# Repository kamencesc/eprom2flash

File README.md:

# untested

# eprom2flash
Use 29F800 flash memory on a 27C800 and 27C160 socket.

**Only works on 16 bit mode!**

# Configure
To use 1 Bank (as a 27C800), use Bank 1 and close jumpers "B1 only".

To use 2 Bank (as a 27c160), use a 74x139 tsop16.

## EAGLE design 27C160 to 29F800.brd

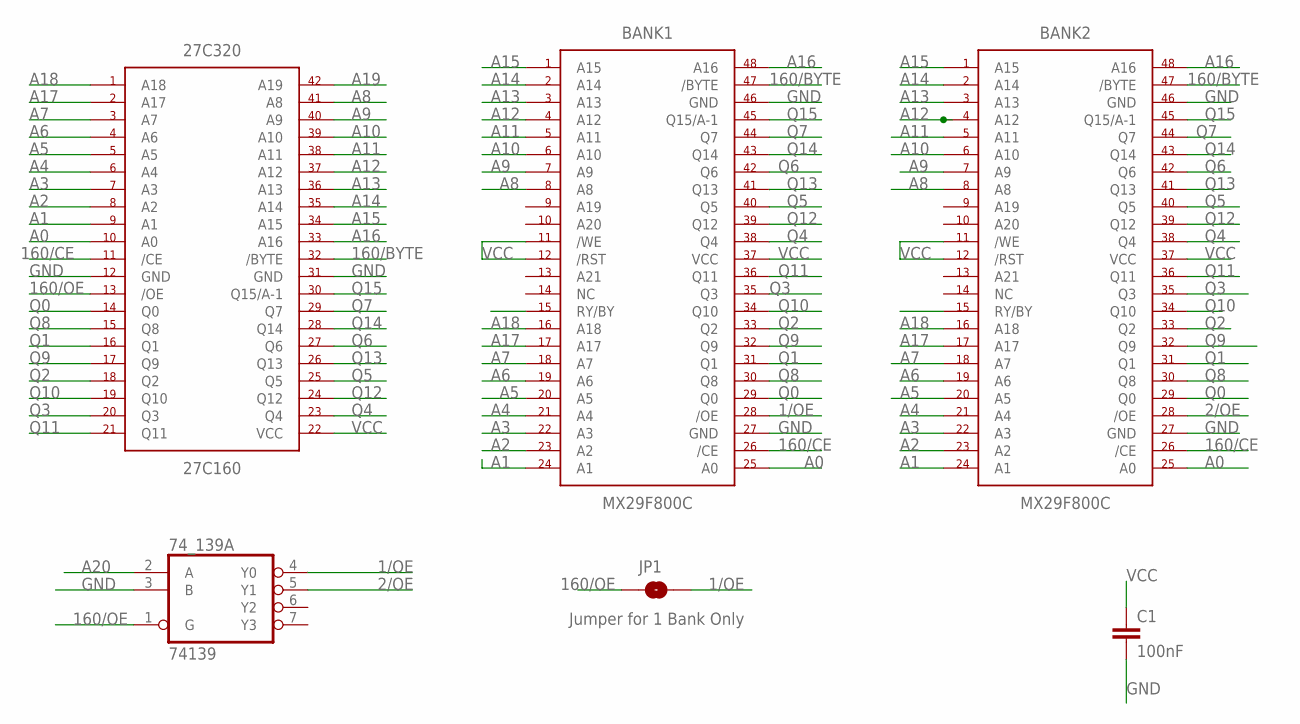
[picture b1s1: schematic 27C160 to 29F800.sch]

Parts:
27C320: 27C160; DIP_600MIL_42
74_139: 74139; TSSOP16
BANK1, BANK2: MX29F800C; TSOP48
C1: 100nF; 0603
JP1: JUMPER-SMT_2_NO_NO-SILK; SMT-JUMPER_2_NO_NO-SILK

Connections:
1/OE: 74_139.4 (Y0), BANK1.P$28 (/OE), JP1.2
2/OE: 74_139.5 (Y1), BANK2.P$28 (/OE)
160/BYTE: 27C320.P$32 (/BYTE), BANK1.P$47 (/BYTE), BANK2.P$47 (/BYTE)
160/CE: 27C320.P$11 (/CE), BANK1.P$26 (/CE), BANK2.P$26 (/CE)
160/OE: 27C320.P$13 (/OE), 74_139.1 (G), JP1.1
A0: 27C320.P$10 (A0), BANK1.P$25 (A0), BANK2.P$25 (A0)
A1: 27C320.P$9 (A1), BANK1.P$24 (A1), BANK2.P$24 (A1)
A2: 27C320.P$8 (A2), BANK1.P$23 (A2), BANK2.P$23 (A2)
A3: 27C320.P$7 (A3), BANK1.P$22 (A3), BANK2.P$22 (A3)
A4: 27C320.P$6 (A4), BANK1.P$21 (A4), BANK2.P$21 (A4)
A5: 27C320.P$5 (A5), BANK1.P$20 (A5), BANK2.P$20 (A5)
A6: 27C320.P$4 (A6), BANK1.P$19 (A6), BANK2.P$19 (A6)
A7: 27C320.P$3 (A7), BANK1.P$18 (A7), BANK2.P$18 (A7)
A8: 27C320.P$41 (A8), BANK1.P$8 (A8), BANK2.P$8 (A8)
A9: 27C320.P$40 (A9), BANK1.P$7 (A9), BANK2.P$7 (A9)
A10: 27C320.P$39 (A10), BANK1.P$6 (A10), BANK2.P$6 (A10)
A11: 27C320.P$38 (A11), BANK1.P$5 (A11), BANK2.P$5 (A11)
A12: 27C320.P$37 (A12), BANK1.P$4 (A12), BANK2.P$4 (A12)
A13: 27C320.P$36 (A13), BANK1.P$3 (A13), BANK2.P$3 (A13)
A14: 27C320.P$35 (A14), BANK1.P$2 (A14), BANK2.P$2 (A14)
A15: 27C320.P$34 (A15), BANK1.P$1 (A15), BANK2.P$1 (A15)
A16: 27C320.P$33 (A16), BANK1.P$48 (A16), BANK2.P$48 (A16)
A17: 27C320.P$2 (A17), BANK1.P$17 (A17), BANK2.P$17 (A17)
A18: 27C320.P$1 (A18), BANK1.P$16 (A18), BANK2.P$16 (A18)
A19: 27C320.P$42 (A19)
A20: 74_139.2 (A)
GND: 27C320.P$12 (GND), 27C320.P$31 (GND), 74_139.3 (B), 74_139.8 (GND), BANK1.P$27 (GND), BANK1.P$46 (GND), BANK2.P$27 (GND), BANK2.P$46 (GND), C1.2
Q0: 27C320.P$14 (Q0), BANK1.P$29 (Q0), BANK2.P$29 (Q0)
Q1: 27C320.P$16 (Q1), BANK1.P$31 (Q1), BANK2.P$31 (Q1)
Q2: 27C320.P$18 (Q2), BANK1.P$33 (Q2), BANK2.P$33 (Q2)
Q3: 27C320.P$20 (Q3), BANK1.P$35 (Q3), BANK2.P$35 (Q3)
Q4: 27C320.P$23 (Q4), BANK1.P$38 (Q4), BANK2.P$38 (Q4)
Q5: 27C320.P$25 (Q5), BANK1.P$40 (Q5), BANK2.P$40 (Q5)
Q6: 27C320.P$27 (Q6), BANK1.P$42 (Q6), BANK2.P$42 (Q6)
Q7: 27C320.P$29 (Q7), BANK1.P$44 (Q7), BANK2.P$44 (Q7)
Q8: 27C320.P$15 (Q8), BANK1.P$30 (Q8), BANK2.P$30 (Q8)
Q9: 27C320.P$17 (Q9), BANK1.P$32 (Q9), BANK2.P$32 (Q9)
Q10: 27C320.P$19 (Q10), BANK1.P$34 (Q10), BANK2.P$34 (Q10)
Q11: 27C320.P$21 (Q11), BANK1.P$36 (Q11), BANK2.P$36 (Q11)
Q12: 27C320.P$24 (Q12), BANK1.P$39 (Q12), BANK2.P$39 (Q12)
Q13: 27C320.P$26 (Q13), BANK1.P$41 (Q13), BANK2.P$41 (Q13)
Q14: 27C320.P$28 (Q14), BANK1.P$43 (Q14), BANK2.P$43 (Q14)
Q15: 27C320.P$30 (Q15/A-1), BANK1.P$45 (Q15/A-1), BANK2.P$45 (Q15/A-1)
VCC: 27C320.P$22 (VCC), 74_139.16 (VCC), BANK1.P$12 (/RST), BANK1.P$37 (VCC), BANK2.P$11 (/WE), BANK2.P$12 (/RST), BANK2.P$37 (VCC), C1.1

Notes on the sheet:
Jumper for 1 Bank Only

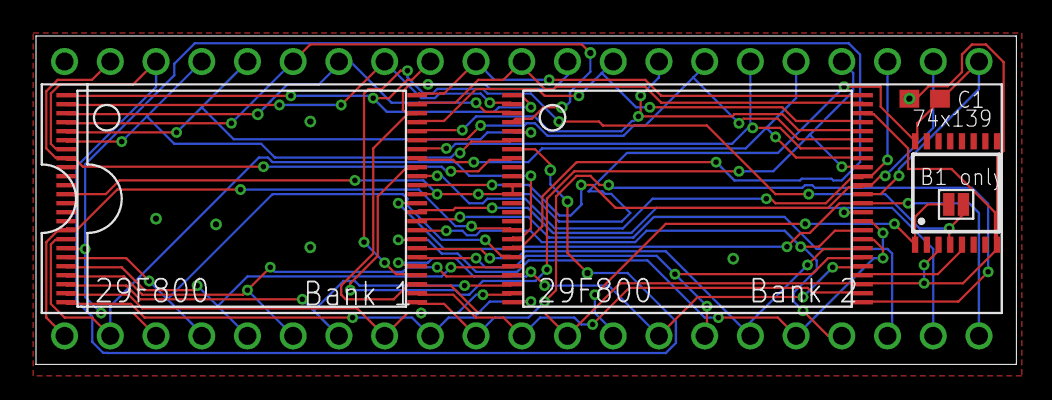
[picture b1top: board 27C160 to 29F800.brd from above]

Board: 2 copper layers, 54.5 x 18.2 mm, 6 parts (0 on the bottom side), 42 nets.

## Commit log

2019-04-14 BRD and SCH
    First release

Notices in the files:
parts and their libraries:
SparkFun-Jumpers: Licensing: Creative Commons ShareAlike 4.0 International - https://creativecommons.org/licenses/by-sa/4.0
